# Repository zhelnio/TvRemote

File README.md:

# TvRemote
1-button TV remote joke from 2013.
Just one command: "Next channel".  
It was designed to troll my wife when she was watching some sitcom.

**Photo**

**Schematic**

**Board**

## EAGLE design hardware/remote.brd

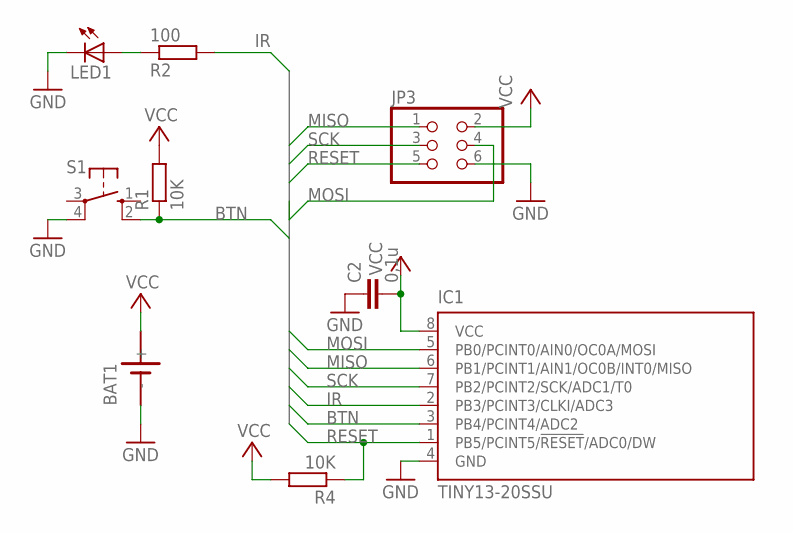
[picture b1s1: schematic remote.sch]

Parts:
BAT1: SN2032
C2: 0,1u; C1206
IC1: TINY13-20SSU; 8S1
JP3: PINHD-2X3_2.54; 2X03
LED1: LED3MM
R1, R4: 10K; R1206
R2: 100; R1206
S1: 10-XX; B3F-10XX

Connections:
BTN: IC1.3 (PB4/PCINT4/ADC2), R1.1, S1.2 (S1)
GND: BAT1.-, C2.1, IC1.4 (GND), JP3.6, LED1.K (C), S1.4 (P1)
IR: IC1.2 (PB3/PCINT3/CLKI/ADC3), R2.2
MISO: IC1.6 (PB1/PCINT1/AIN1/OC0B/INT0/MISO), JP3.1
MOSI: IC1.5 (PB0/PCINT0/AIN0/OC0A/MOSI), JP3.4
unnamed: LED1.A, R2.1
RESET: IC1.1 (PB5/PCINT5/!RESET!/ADC0/DW), JP3.5, R4.1
SCK: IC1.7 (PB2/PCINT2/SCK/ADC1/T0), JP3.3
VCC: BAT1.+, C2.2, IC1.8 (VCC), JP3.2, R1.2, R4.2

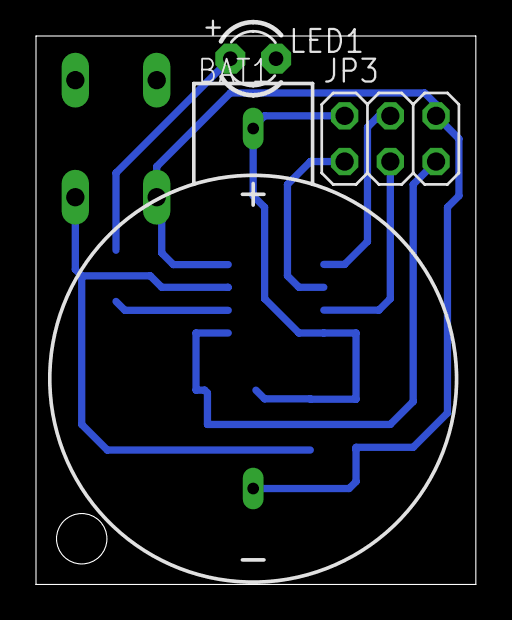
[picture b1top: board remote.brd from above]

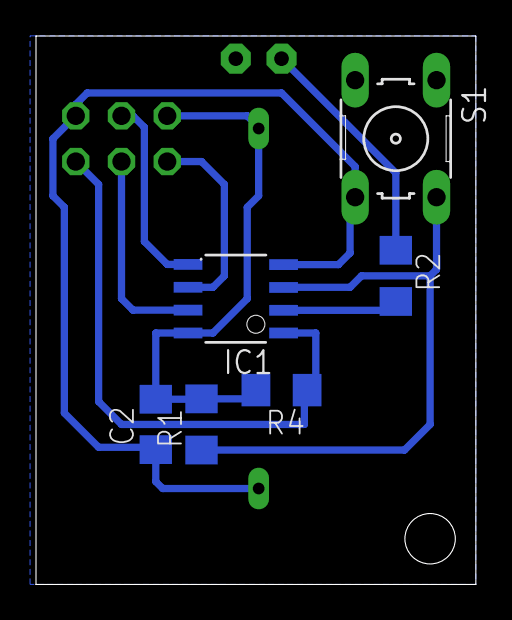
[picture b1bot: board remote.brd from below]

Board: 2 copper layers, 24.4 x 30.5 mm, 9 parts (6 on the bottom side), 9 nets.

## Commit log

2017-06-30 :octocat: Added .gitattributes & .gitignore files
2017-06-30 firmware added
2017-06-30 board added
2017-06-30 docs added
2017-06-30 image resize
2017-06-30 Create LICENSE
